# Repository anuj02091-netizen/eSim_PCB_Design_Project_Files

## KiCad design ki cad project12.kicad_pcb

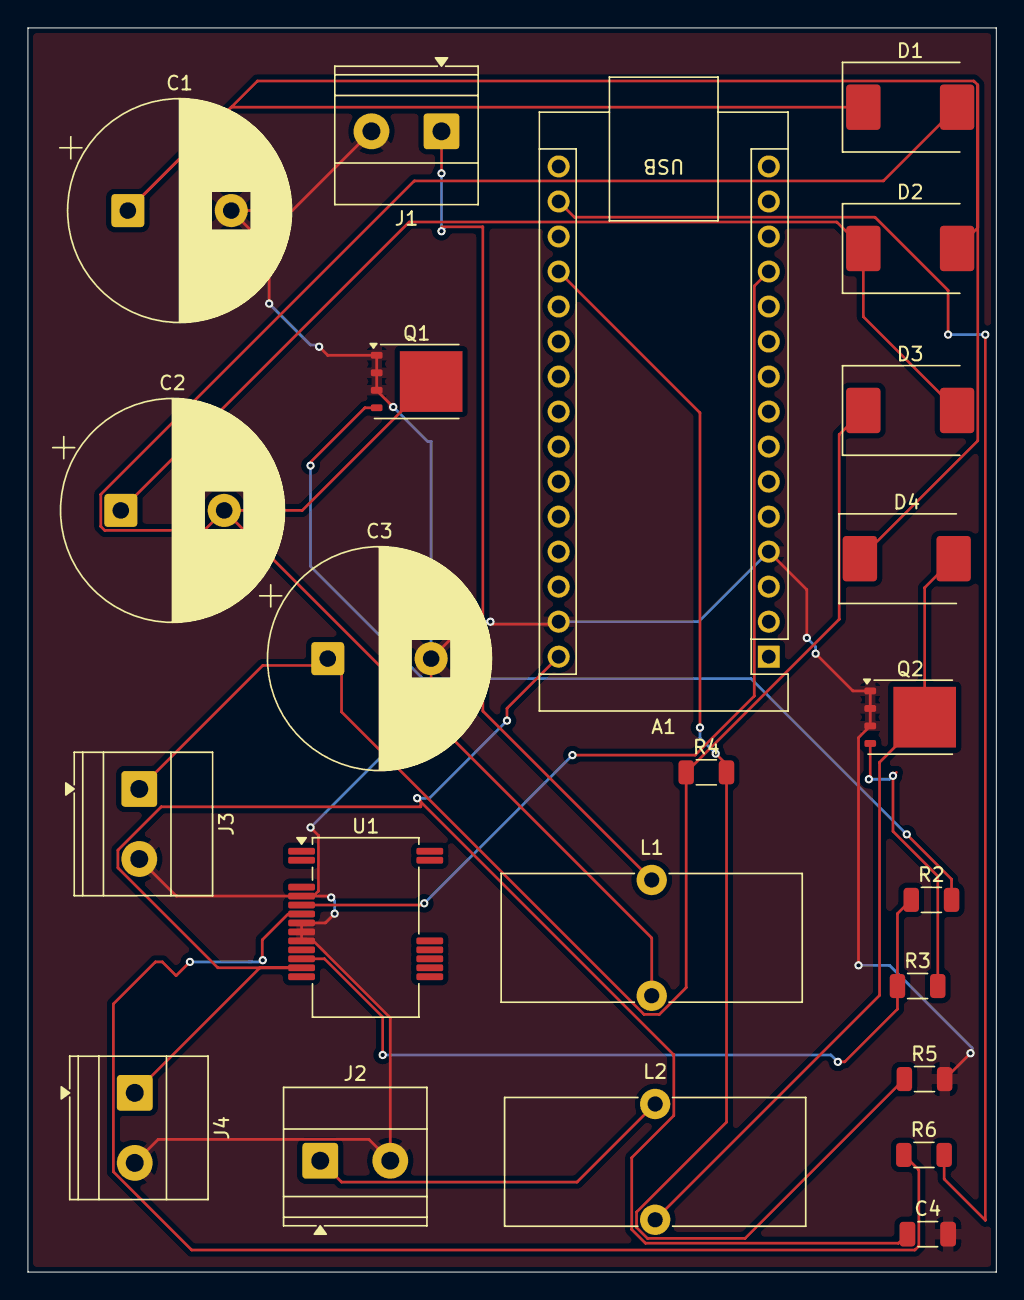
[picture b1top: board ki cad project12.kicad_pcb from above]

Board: 2 copper layers, 70.2 x 90.2 mm, 23 parts (0 on the bottom side), 16 nets.

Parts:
A1: Arduino_Nano_RP2040_Connect; Arduino_Nano
C1, C2, C3: C; CP_Radial_D16.0mm_P7.50mm
C4: C; C_1206_3216Metric
D1, D2, D3, D4: D; D_SMC
J1, J2, J3: Screw_Terminal_01x02; TerminalBlock_Phoenix_MKDS-1,5-2-5.08_1x02_P5.08mm_Horizont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
J4: 12v; TerminalBlock_Phoenix_MKDS-1,5-2-5.08_1x02_P5.08mm_Horizont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
L1, L2: L; L_Toroid_Vertical_L21.6mm_W9.1mm_P8.40mm_Bourns_5700
Q1, Q2: BSC340N08NS3G; TDSON-8-1
R2, R3: 10; R_1206_3216Metric
R4: 270k; R_1206_3216Metric
R5: 4.7k; R_1206_3216Metric
R6: 10k; R_1206_3216Metric
U1: 2ED1323S12P; Infineon_PG-DSO-20-U03_7.5x12.8mm

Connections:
/drv: R2.1, R3.1, U1.11 (LO)
/fb: A1.19 (A0), R4.2, R5.1
/g1: Q1.4 (G), R2.2
/g2: Q2.4 (G), R3.2
/out1: C1.1, D1.1 (K), D2.2 (A), D4.1 (K)
/out2: C3.1, D3.1 (K), J3.1, R4.1
/pwm: A1.12 (D9), U1.5 (LIN)
/rfe: R6.1, U1.6 (~RFE)
/sw1: C2.2, D1.2 (A), L1.2, Q1.5 (D)
/v12: A1.30 (VIN), C4.1, J4.1, U1.12 (VCC)
/v33: A1.17 (3V3), R6.2
GND: A1.4 (GND), A1.29 (GND), C1.2, C3.2, C4.2, J1.2, J2.2, J3.2, J4.2, Q1.1 (S), Q1.2 (S), Q1.3 (S), Q2.1 (S), Q2.2 (S), Q2.3 (S), R5.2, U1.4 (HIN), U1.7 (VSS), U1.8 (ITRIP), U1.9 (COM)
unnamed: C2.1, D2.1 (K), D3.2 (A)
unnamed: D4.2 (A), L2.2, Q2.5 (D)
unnamed: J1.1, L1.1
unnamed: J2.1, L2.1
